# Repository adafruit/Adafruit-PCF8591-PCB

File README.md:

## Adafruit PCF8591 ADC+DAC PCB

<a href="http://www.adafruit.com/products/4648"><br/>
Click here to purchase one from the Adafruit shop</a>

PCB files for the Adafruit PCF8591 ADC+DAC. 

Format is EagleCAD schematic and board layout
* https://www.adafruit.com/product/4648

### Description

Measuring voltage and adjusting it is what electronics is all about so you won’t get far without friends like the PCF8591 ADC+DAC combo.  Analog to Digital Converters help by measuring an analog voltage and turning it into something a microcontroller like a Metro or Arduino 
can understand. If you’re using a single board computer like a Raspberry Pi, you might not have any other way to measure a voltage because even though they are well equipped for digital circuits, many boards of that type don’t have any pins that can measure analog voltages. 
Adding a PCF8591 to your electronics project will give you not one, not two but four analog inputs that you can use to measure voltages from. If knobs are just the thing to complete your project, just add a PCF8591 and some potentiometers and you’re ready to twist, turn, twiddle and tweak to get things just right

Along with four 8-bit ADC channels, the PCF8591 comes complete with a Digital to Analog Converter converter as well! Not only can you measure voltages, but now you can create them just as you want them. You can even use the DAC and ADC together to create an input to a circuit and measure the results with the ADC. The possibilities abound! “Wow” you say,”That sounds great, but surely with all that fun in one small packages, I can only use one at a time.” Well my friend, I’ve got good news. On the back of each PCF8591 breakout are three jumpers that allow you to set the I2C address, allowing the use of eight PCF8591s on the same I2C bus! That’s up to a a whopping 32 channels of analog measurement and 8 channels of analog signal generation!
If you do decide to go all out with your project, you won’t break the bank because the PCF8591 breakouts are reasonably priced compared to some higher-end ADCs.

As if 4 ADCs and one DAC in a single package weren’t enough, we’ve made it even easier to use by mounting the PCF8591 chonky SO16 surface mount package onto a breakout with standard 0.1”/2.54mm headers and  SparkFun Qwiic compatible STEMMA QT connectors for the I2C bus, making it simple to integrate with your project. Using the wiring diagrams and example code on the pages that follow, you’ll be able to use our Python and Arduino libraries to easily measure as many voltages as you need (as long as that number is 32 or less).

### License

Adafruit invests time and resources providing this open source design, please support Adafruit and open-source hardware by purchasing products from [Adafruit](https://www.adafruit.com)!

Designed by Limor Fried/Ladyada for Adafruit Industries.

Creative Commons Attribution/Share-Alike, all text above must be included in any redistribution. 
See license.txt for additional details.

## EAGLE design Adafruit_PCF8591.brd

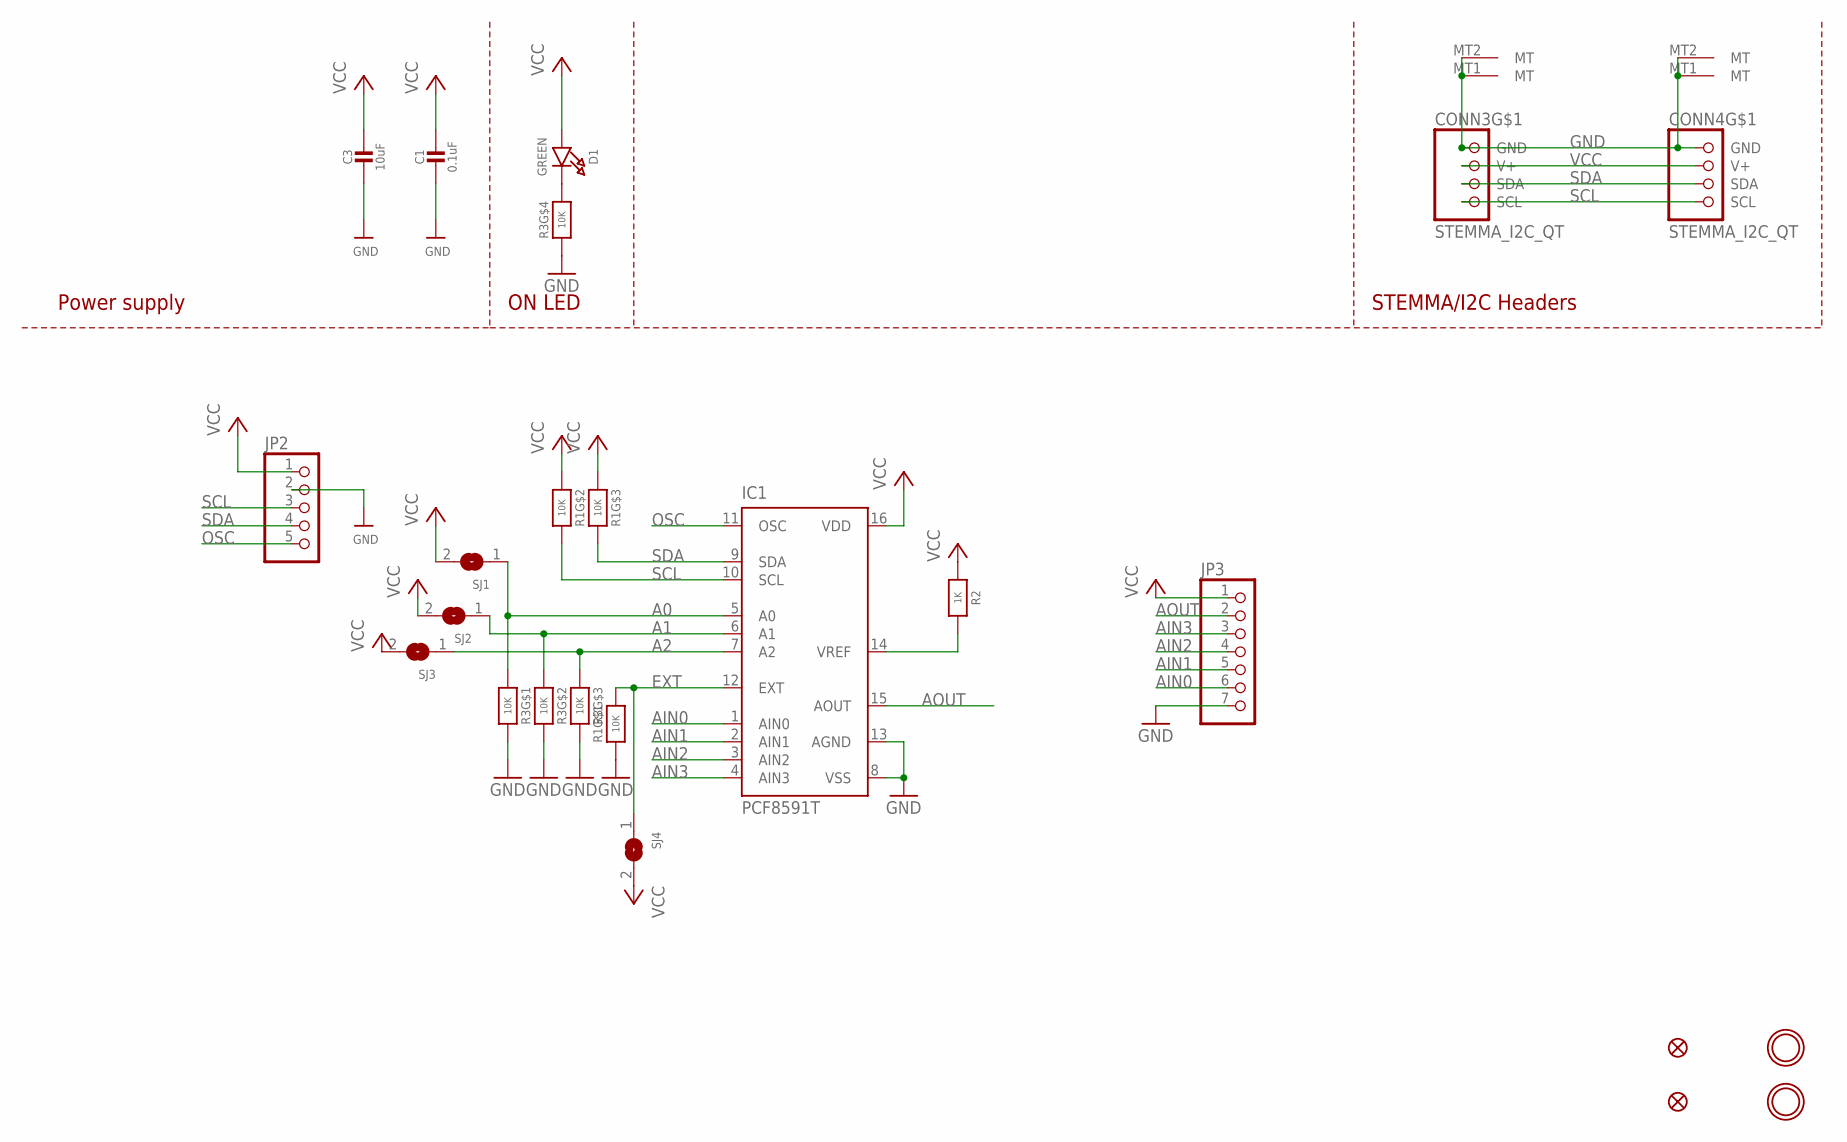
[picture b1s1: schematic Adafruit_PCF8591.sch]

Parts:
C1: 0.1uF; 0603-NO
C3: 10uF; 0805-NO
CONN3, CONN4: STEMMA_I2C_QT; JST_SH4
D1: GREEN; CHIPLED_0603_NOOUTLINE
FID3, FID4: FIDUCIAL_1MM
IC1: PCF8591T; SO16W
JP2: HEADER-1X570MIL; 1X05_ROUND_70
JP3: HEADER-1X770MIL; 1X07_ROUND_70
R1, R3: 10K; RESPACK_4X0603
R2: 1K; 0603-NO
SJ1, SJ2, SJ3, SJ4: SOLDERJUMPER; SOLDERJUMPER_ARROW_NOPASTE
U$19, U$21: MOUNTINGHOLE2.5; MOUNTINGHOLE_2.5_PLATED

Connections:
A0: IC1.5 (A0), R3.1, SJ1.1
A1: IC1.6 (A1), R3.2 (1), SJ2.1
A2: IC1.7 (A2), R3.3 (1), SJ3.1
AIN0: IC1.1 (AIN0), JP3.6
AIN1: IC1.2 (AIN1), JP3.5
AIN2: IC1.3 (AIN2), JP3.4
AIN3: IC1.4 (AIN3), JP3.3
AOUT: IC1.15 (AOUT), JP3.2
EXT: IC1.12 (EXT), R1.8 (2), SJ4.1
GND: C1.2, C3.2, CONN3.1 (GND), CONN3.MT1 (MT), CONN3.MT2 (MT), CONN4.1 (GND), CONN4.MT1 (MT), CONN4.MT2 (MT), IC1.8 (VSS), IC1.13 (AGND), JP2.2, JP3.7, R1.1, R3.4 (1), R3.6 (2), R3.7 (2), R3.8 (2)
unnamed: D1.C, R3.5 (2)
unnamed: IC1.14 (VREF), R2.2
OSC: IC1.11 (OSC), JP2.5
SCL: CONN3.4 (SCL), CONN4.4 (SCL), IC1.10 (SCL), JP2.3, R1.7 (2)
SDA: CONN3.3 (SDA), CONN4.3 (SDA), IC1.9 (SDA), JP2.4, R1.6 (2)
VCC: C1.1, C3.1, CONN3.2 (V+), CONN4.2 (V+), D1.A, IC1.16 (VDD), JP2.1, JP3.1, R1.2 (1), R1.3 (1), R2.1, SJ1.2, SJ2.2, SJ3.2, SJ4.2

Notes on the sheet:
STEMMA/I2C Headers
ON LED
Power supply

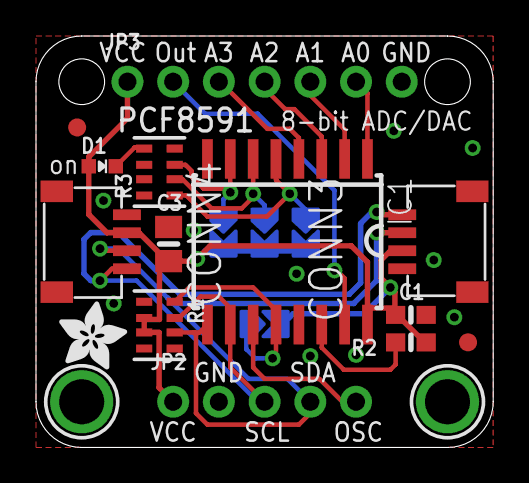
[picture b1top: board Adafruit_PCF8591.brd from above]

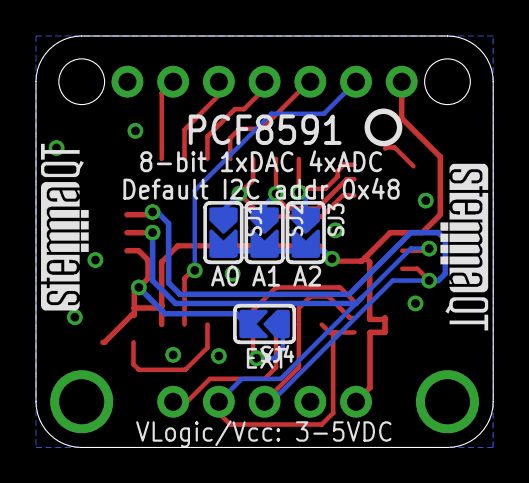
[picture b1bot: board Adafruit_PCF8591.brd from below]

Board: 2 copper layers, 25.4 x 22.9 mm, 23 parts (7 on the bottom side), 16 nets.

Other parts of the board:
U$22: ADAFRUIT_3.5MM
U$25: PCBFEAT-REV-040
U$30, U$31: STEMMAQT

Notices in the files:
parts and their libraries:
microbuilder: This work is placed in the public domain, and may be freely used for commercial and non-commercial work with the following conditions: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
